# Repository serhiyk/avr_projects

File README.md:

# Arduino clock

### Component list

 * Arduino pro mini
 * Display modules based on MAX7219 (6x2)
 * RTC based on DS3231
 * PIR sensor (optional)
 * Light sensor (optional)

### Compiling the source

I've tested the compiling process only on Ubuntu 14.04

#### Install the required software:

`sudo apt-get install gcc-avr`
`sudo apt-get install avr-libc`
`sudo apt-get install avrdude`

#### Compile the source:

`cd src/clock_6x2/`
`make all`

#### Upload FW to the device:

`sudo make upload`

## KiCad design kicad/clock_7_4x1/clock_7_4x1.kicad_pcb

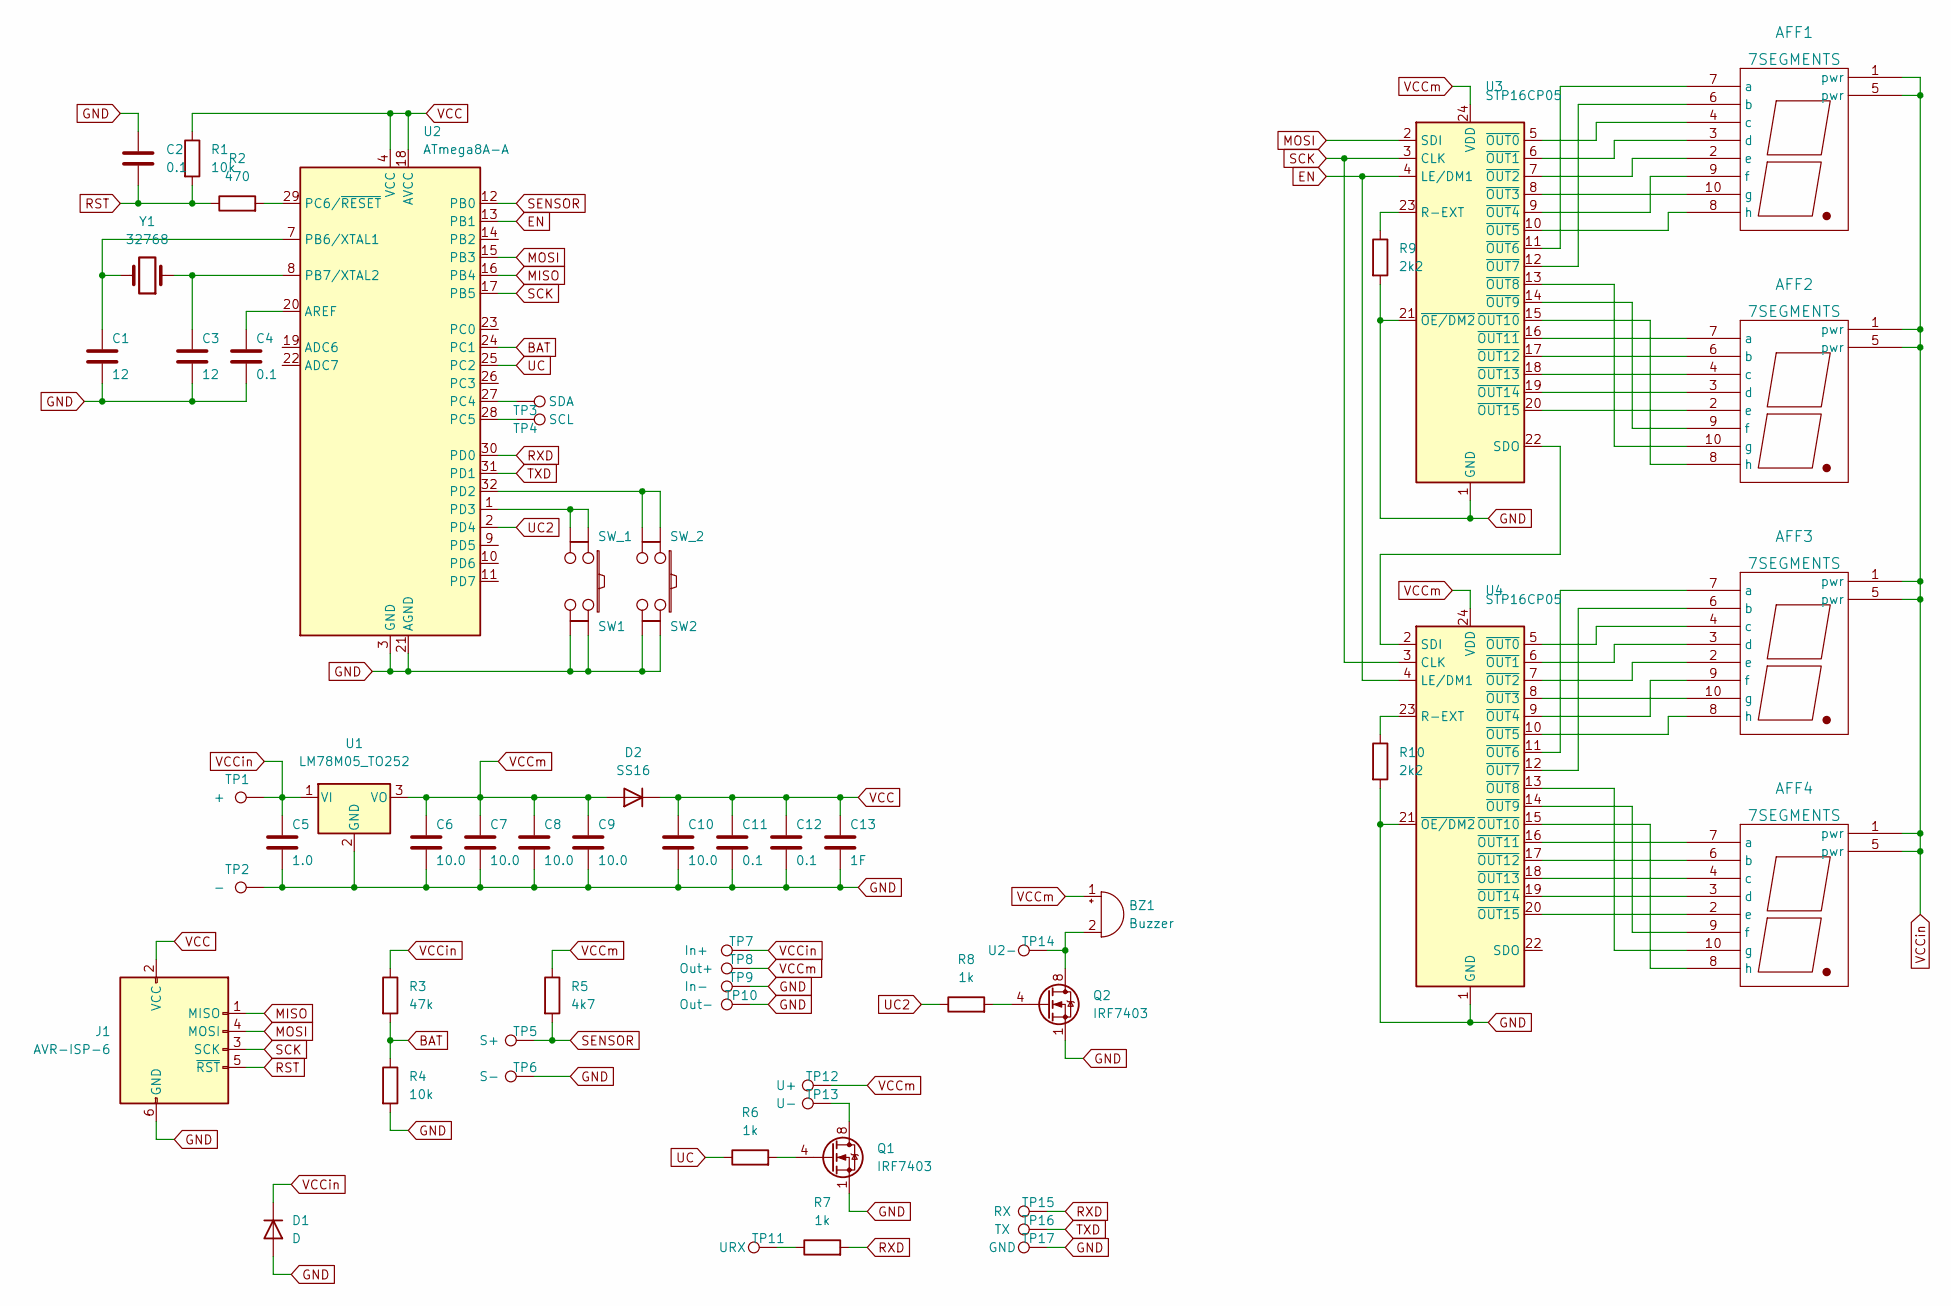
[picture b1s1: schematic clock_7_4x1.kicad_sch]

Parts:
AFF1, AFF2, AFF3, AFF4: 7SEGMENTS; AFF_S2306
BZ1: Buzzer; Buzzer_12x9.5RM7.6
C1, C3: 12; C_0805_2012Metric
C2, C4, C11, C12: 0.1; C_0805_2012Metric
C5: 1.0; C_0805_2012Metric
C6, C7, C8, C9, C10: 10.0; C_1210_3225Metric
C13: 1F; BatteryHolder_ComfortableElectronic_CH273-2450_1x2450
D1: D; D_DO-15_P15.24mm_Horizontal
D2: SS16; D_SMA_Handsoldering
J1: AVR-ISP-6; IDC-Header_2x03_P2.54mm_Vertical
Q1, Q2: IRF7403; SOIC-8_3.9x4.9mm_P1.27mm
R1, R4: 10k; R_0805_2012Metric
R2: 470; R_0805_2012Metric
R3: 47k; R_0805_2012Metric
R5: 4k7; R_0805_2012Metric
R6, R7, R8: 1k; R_0805_2012Metric
R9, R10: 2k2; R_0805_2012Metric
SW1: SW_1
SW2: SW_2; SW_1
TP1: +; TestPoint_Pad_4.0x4.0mm
TP2: -; TestPoint_Pad_4.0x4.0mm
TP3: SDA; TestPoint_Pad_4.0x4.0mm
TP4: SCL; TestPoint_Pad_4.0x4.0mm
TP5: S+; TestPoint_Pad_4.0x4.0mm
TP6: S-; TestPoint_Pad_4.0x4.0mm
TP7: In+; TestPoint_Pad_4.0x4.0mm
TP8: Out+; TestPoint_Pad_4.0x4.0mm
TP9: In-; TestPoint_Pad_4.0x4.0mm
TP10: Out-; TestPoint_Pad_4.0x4.0mm
TP11: URX; TestPoint_Pad_4.0x4.0mm
TP12: U+; TestPoint_Pad_4.0x4.0mm
TP13: U-; TestPoint_Pad_4.0x4.0mm
TP14: U2-; TestPoint_Pad_4.0x4.0mm
TP15: RX; TestPoint_Pad_4.0x4.0mm
TP16: TX; TestPoint_Pad_4.0x4.0mm
TP17: GND; TestPoint_Pad_4.0x4.0mm
U1: LM78M05_TO252; TO-252-2
U2: ATmega8A-A; TQFP-32_7x7mm_P0.8mm
U3, U4: STP16CP05; SO-24_5.3x15mm_P1.27mm
Y1: 32768; Crystal_AT310_D3.0mm_L10.0mm_Horizontal

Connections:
BAT: R3.2, R4.1, U2.24 (PC1)
EN: U2.13 (PB1), U3.4 (LE/DM1), U4.4 (LE/DM1)
GND: C1.2, C2.1, C3.2, C4.2, C5.2, C6.2, C7.2, C8.2, C9.2, C10.2, C11.2, C12.2, C13.2, D1.2 (A), J1.6 (GND), Q1.1 (S), Q1.2 (S), Q1.3 (S), Q2.1 (S), Q2.2 (S), Q2.3 (S), R4.2, R9.2, R10.2, SW1.3, SW1.4, SW2.3, SW2.4, TP2.1, TP6.1, TP9.1, TP10.1, TP17.1, U1.2 (GND), U2.3 (GND), U2.5 (GND), U2.21 (AGND), U3.1 (GND), U3.21 (~OE/DM2), U4.1 (GND), U4.21 (~OE/DM2)
MISO: J1.1 (MISO), U2.16 (PB4)
MOSI: J1.4 (MOSI), U2.15 (PB3), U3.2 (SDI)
unnamed: AFF1.2 (e), U3.7 (~OUT2)
unnamed: AFF1.3 (d), U3.6 (~OUT1)
unnamed: AFF1.4 (c), U3.5 (~OUT0)
unnamed: AFF1.6 (b), U3.12 (~OUT7)
unnamed: AFF1.7 (a), U3.11 (~OUT6)
unnamed: AFF1.8 (h), U3.10 (~OUT5)
unnamed: AFF1.9 (f), U3.9 (~OUT4)
unnamed: AFF1.10 (g), U3.8 (~OUT3)
unnamed: AFF2.2 (e), U3.20 (~OUT15)
unnamed: AFF2.3 (d), U3.19 (~OUT14)
unnamed: AFF2.4 (c), U3.18 (~OUT13)
unnamed: AFF2.6 (b), U3.17 (~OUT12)
unnamed: AFF2.7 (a), U3.16 (~OUT11)
unnamed: AFF2.8 (h), U3.15 (~OUT10)
unnamed: AFF2.9 (f), U3.14 (~OUT9)
unnamed: AFF2.10 (g), U3.13 (~OUT8)
unnamed: AFF3.2 (e), U4.7 (~OUT2)
unnamed: AFF3.3 (d), U4.6 (~OUT1)
unnamed: AFF3.4 (c), U4.5 (~OUT0)
unnamed: AFF3.6 (b), U4.12 (~OUT7)
unnamed: AFF3.7 (a), U4.11 (~OUT6)
unnamed: AFF3.8 (h), U4.10 (~OUT5)
unnamed: AFF3.9 (f), U4.9 (~OUT4)
unnamed: AFF3.10 (g), U4.8 (~OUT3)
unnamed: AFF4.2 (e), U4.20 (~OUT15)
unnamed: AFF4.3 (d), U4.19 (~OUT14)
unnamed: AFF4.4 (c), U4.18 (~OUT13)
unnamed: AFF4.6 (b), U4.17 (~OUT12)
unnamed: AFF4.7 (a), U4.16 (~OUT11)
unnamed: AFF4.8 (h), U4.15 (~OUT10)
unnamed: AFF4.9 (f), U4.14 (~OUT9)
unnamed: AFF4.10 (g), U4.13 (~OUT8)
unnamed: BZ1.2 (+), Q2.5 (D), Q2.6 (D), Q2.7 (D), Q2.8 (D), TP14.1
unnamed: C1.1, U2.7 (PB6/XTAL1), Y1.2
unnamed: C3.1, U2.8 (PB7/XTAL2), Y1.1
unnamed: C4.1, U2.20 (AREF)
unnamed: Q1.4 (G), R6.2
unnamed: Q1.5 (D), Q1.6 (D), Q1.7 (D), Q1.8 (D), TP13.1
unnamed: Q2.4 (G), R8.2
unnamed: R2.2, U2.29 (PC6/~RESET)
unnamed: R7.1, TP11.1
unnamed: R9.1, U3.23 (R-EXT)
unnamed: R10.1, U4.23 (R-EXT)
unnamed: SW1.1, SW1.2, U2.1 (PD3)
unnamed: SW2.1, SW2.2, U2.32 (PD2)
unnamed: TP3.1, U2.27 (PC4)
unnamed: TP4.1, U2.28 (PC5)
unnamed: U3.22 (SDO), U4.2 (SDI)
RST: C2.2, J1.5 (~RST), R1.2, R2.1
RXD: R7.2, TP15.1, U2.30 (PD0)
SCK: J1.3 (SCK), U2.17 (PB5), U3.3 (CLK), U4.3 (CLK)
SENSOR: R5.2, TP5.1, U2.12 (PB0)
TXD: TP16.1, U2.31 (PD1)
UC: R6.1, U2.25 (PC2)
UC2: R8.1, U2.2 (PD4)
VCC: C10.1, C11.1, C12.1, C13.1, D2.1 (K), J1.2 (VCC), R1.1, U2.4 (VCC), U2.6 (VCC), U2.18 (AVCC)
VCCin: AFF1.1 (pwr), AFF1.5 (pwr), AFF2.1 (pwr), AFF2.5 (pwr), AFF3.1 (pwr), AFF3.5 (pwr), AFF4.1 (pwr), AFF4.5 (pwr), C5.1, D1.1 (K), R3.1, TP1.1, TP7.1, U1.1 (VI)
VCCm: BZ1.1 (-), C6.1, C7.1, C8.1, C9.1, D2.2 (A), R5.1, TP8.1, TP12.1, U1.3 (VO), U3.24 (VDD), U4.24 (VDD)

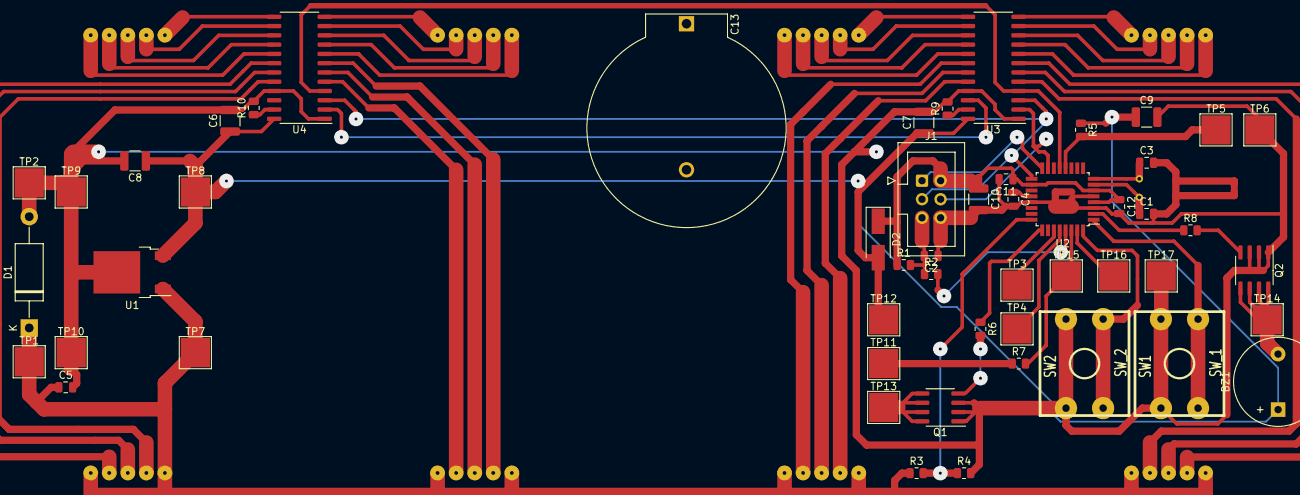
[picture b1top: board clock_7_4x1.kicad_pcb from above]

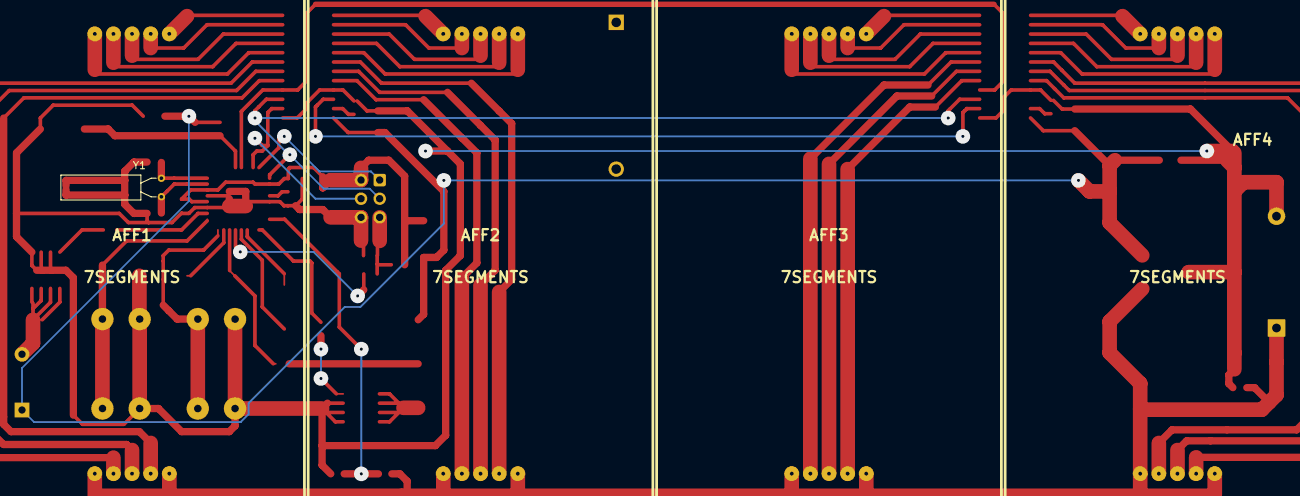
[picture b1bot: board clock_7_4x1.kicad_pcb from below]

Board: 2 copper layers, 57 parts (5 on the bottom side), 63 nets.

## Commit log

2015-01-27 Added src
2015-06-14 Created table for months.
2015-07-19 Made changes in makefile for avrdude
2015-07-19 Implemented command for reset arduino
2015-11-15 Reworked twi driver
2016-03-14 Reworked TWI driver. Reworked DS3231 driver. Made code clean up.
2016-03-15 Reworked SPI driver.
2016-03-15 Made code clean up.
2016-03-19 Reworked display driver. Made code clean up.
2016-03-26 Implemented timer. Updated display driver.
2016-03-27 Moved motion sensor handler to motion.c
2016-03-27 Added config define for motion sensor.
2016-03-31 Implemented serial protocol handler.
2016-04-02 Added command for setting time.
2016-04-26 Split application and drivers.
2016-04-26 Moved command_set_time to DS3231 driver.
2016-05-07 Cleanup
2016-05-07 Updated readme file
2016-05-17 Added blocking SPI transfer function.
2016-05-17 Added test application for nrf24l01
2016-05-21 WIP on nrf24l01 driver
2016-05-29 WIP on nrf24l01 driver. Added config file.
2016-06-12 Added 1wire driver
2016-06-12 Added DS18B20 driver
2016-07-13 Moved display driver.
2016-07-13 Added sensor application
2016-07-13 Added support for remote temperature sensor
2016-07-13 Fixed makefile
2016-07-15 Fixed makefiles
2016-07-15 Moved timer configuration to config file
2016-07-15 Added timeout for remote sensor data
2016-07-30 Split display driver and MAX7219 driver.
2016-08-10 Fixed SPI driver.
2016-08-27 Reworked motion handler.
2016-10-08 Implemented detecting Winter/Summer time.
2016-10-08 Added script for setting time.
2016-10-09 Updated printing temperature.
2016-10-09 Fixed RTC alarm.
2016-10-09 Enabled 2 bytes CRC
2016-10-16 Updated ds18b20 driver
2016-10-16 Added clock_4x1 project
2016-11-13 Added driver for bmp180.
2017-02-05 Added kb project.
2017-04-08 Updated serial protocol.
2017-10-01 Reset config when display is deactivated.
2018-02-10 updated kb
2018-07-29 Small changes
2019-02-07 added kb for stm32
2019-02-09 updated kb for stm32
2019-05-11 Added clock_6x2_vms
2019-05-11 Added dcf77 driver
2019-05-11 Added script for fonts
2019-07-10 added neo7m driver
2019-08-25 Added clock 4x1 gps
2021-04-30 Added solar lamp project
2021-05-06 updated voltage
2022-05-24 Added kicad project
2022-06-11 Add some projects
2024-01-28 added epaper app
2024-01-29 added readme
2024-01-29 added gitattributes
2024-01-29 added photo
2024-01-29 fixed localtime
2024-04-13 added bme680 lib
2024-04-17 Added BME680 app
2024-04-17 Added BME680 app for arduino
2024-04-18 fixed temperature
2025-07-06 added temperature sensor
